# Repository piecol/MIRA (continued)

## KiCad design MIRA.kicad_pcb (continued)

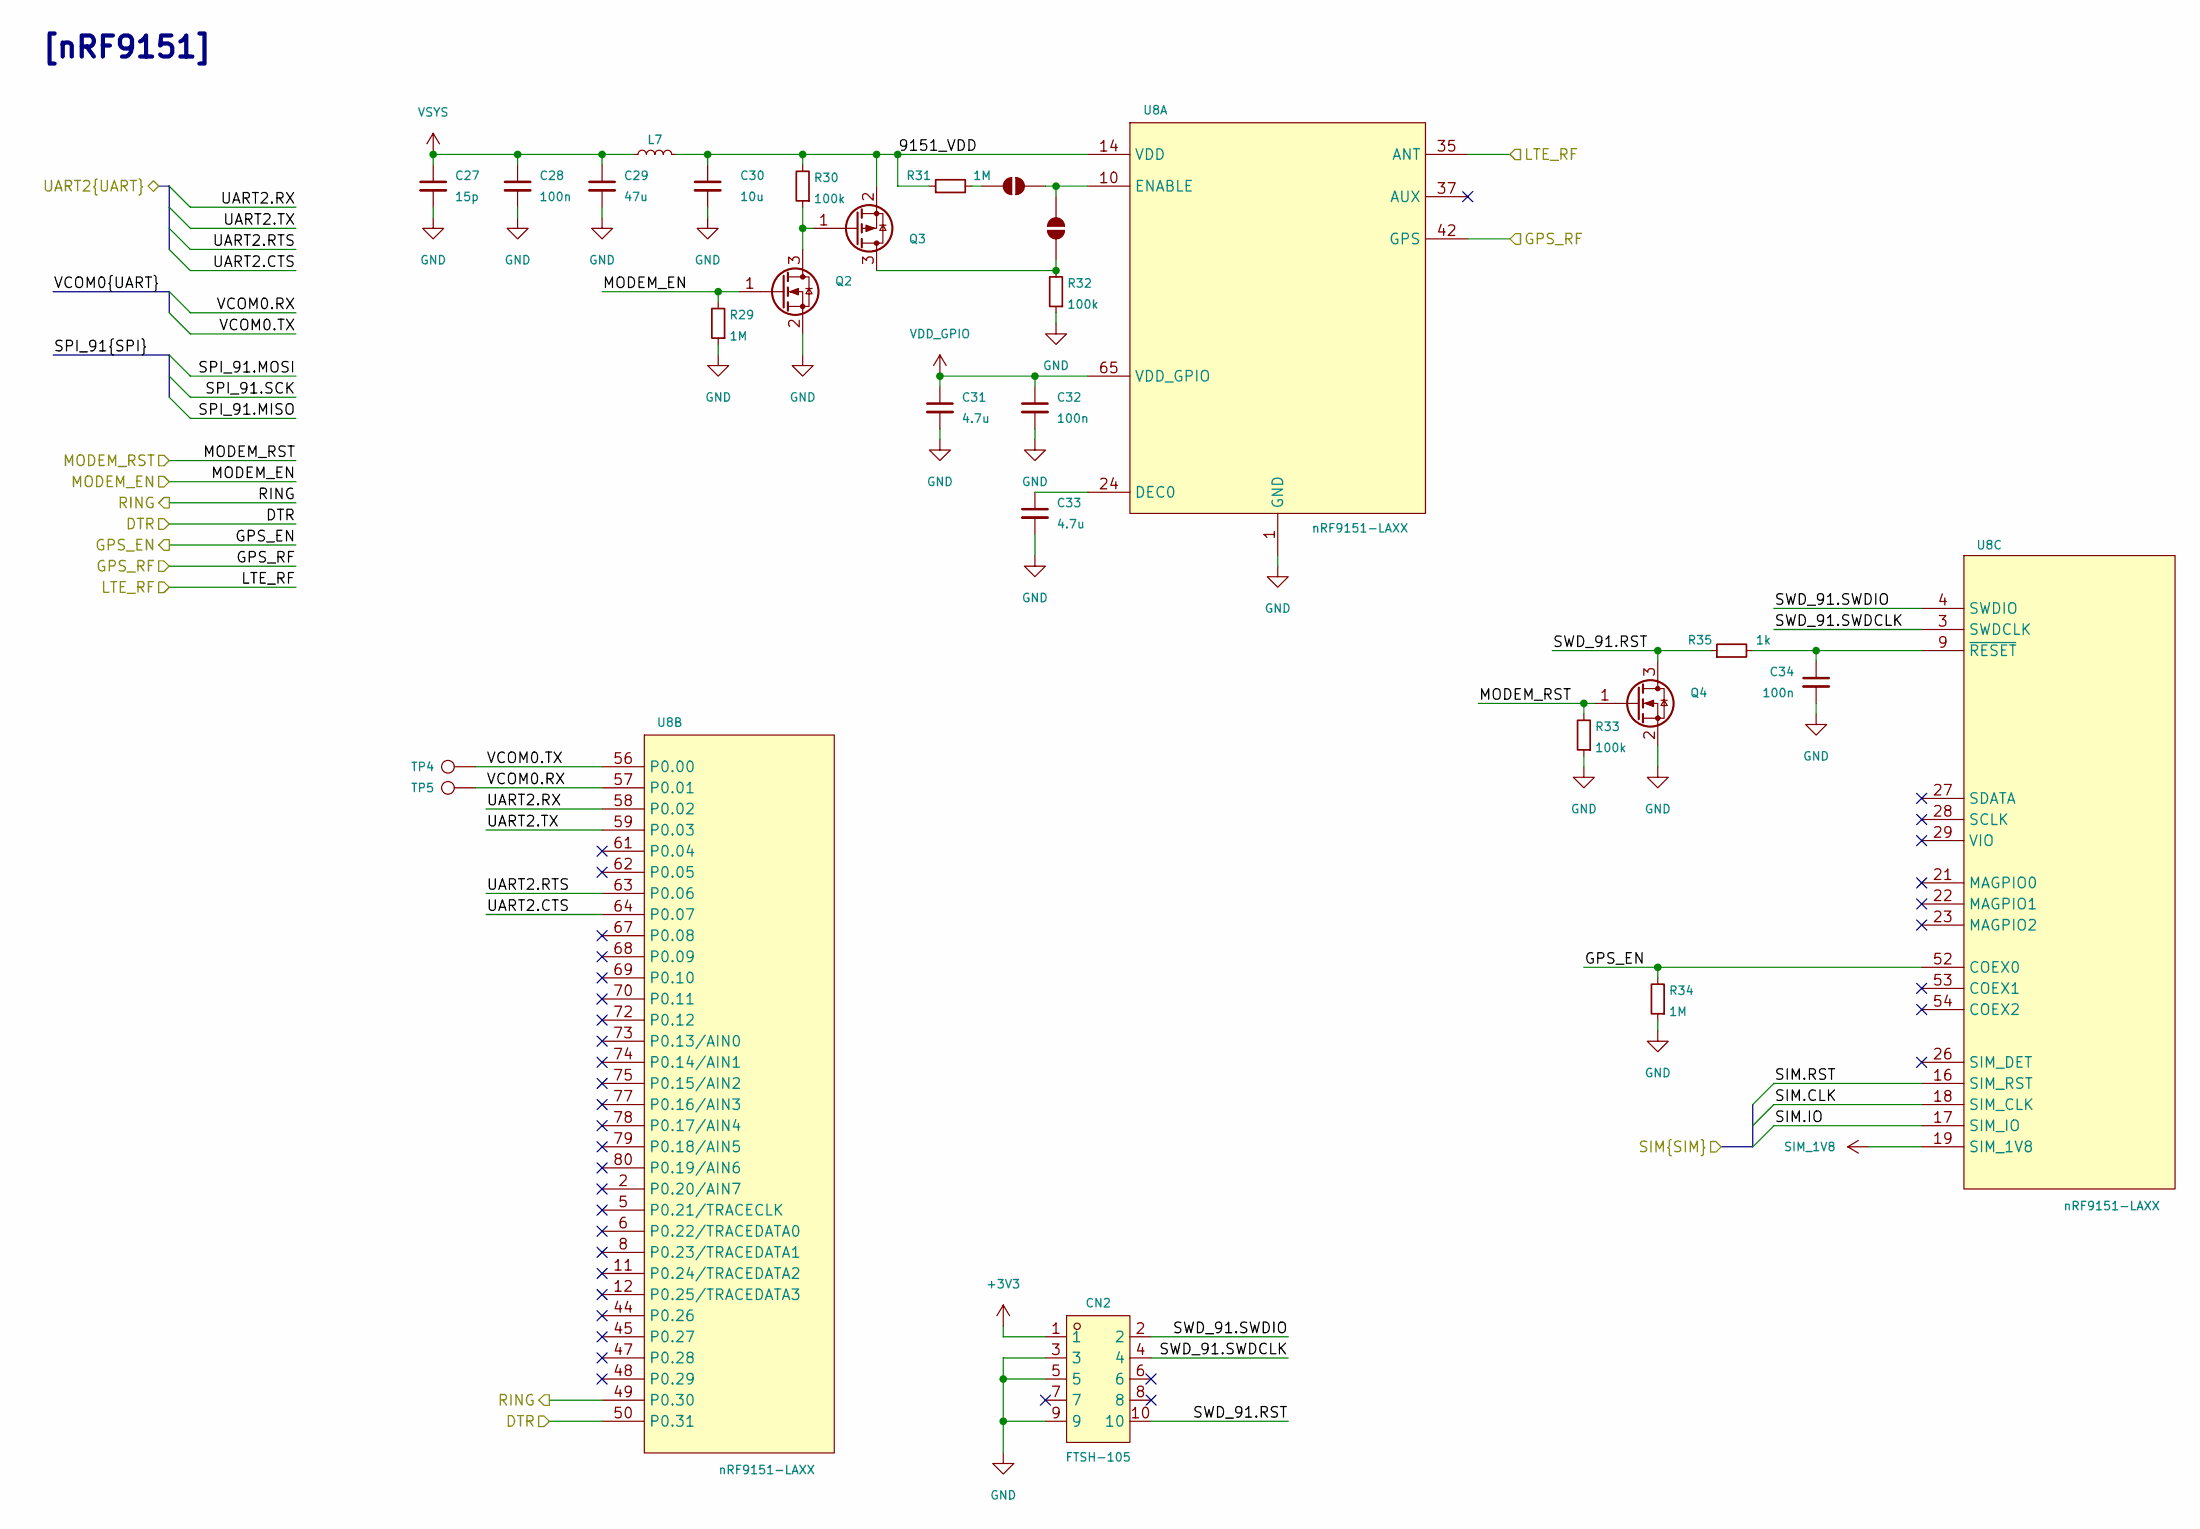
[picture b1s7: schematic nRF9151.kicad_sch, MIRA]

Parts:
C27: 15p; C_0402_1005Metric; LCSC C1548
C28, C32, C34: 100n; C_0402_1005Metric; LCSC C1525
C29: 47u; C_0805_2012Metric; LCSC C16780
C30: 10u; C_0402_1005Metric; LCSC C15525
C31, C33: 4.7u; C_0603_1608Metric; LCSC C19666
CN2: FTSH-105; CONN-SMD_FTSH-105-01-L-DV-K-TR; LCSC Part C448647
JP6, JP7: SolderJumper_2_Open; SolderJumper_Mini
L7: BLM15PX121SN1D; L_0402_1005Metric; LCSC Part C88970
Q2, Q4: DMN2990UFA-7B; XFDFN-3_L0.8-W0.6-P0.35-BR; MPN DMN2990UFA-7B; LCSC Part C151598
Q3: DMP22D4UFA-7B; X2-DFN0806-3_L0.8-W0.6-P0.35-BR; MPN DMP22D4UFA-7B; LCSC Part C2983692
R29, R31, R34: 1M; R_0402_1005Metric; LCSC C26083
R30, R32, R33: 100k; R_0402_1005Metric; LCSC C25741
R35: 1k; R_0402_1005Metric; LCSC C11702
TP4, TP5: TestPoint; TestPoint_Pad_D1.0mm
U8: nRF9151-LAXX; LGA_9151_12.1x11.1mm; LCSC C22397843

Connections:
+3V3: CN2.1; also elsewhere on the board
/RF/GPS_EN: R34.2, U8.52 (COEX0); also elsewhere on the board
/RF/GPS_RF: U8.42 (GPS); also elsewhere on the board
/RF/LTE_RF: U8.35 (ANT); also elsewhere on the board
/SIM/SIM.CLK: U8.18 (SIM_CLK); also elsewhere on the board
/SIM/SIM.IO: U8.17 (SIM_IO); also elsewhere on the board
/SIM/SIM.RST: U8.16 (SIM_RST); also elsewhere on the board
/nRF54L/DTR: U8.50 (P0.31); also elsewhere on the board
/nRF54L/MODEM_EN: Q2.1 (G), R29.2; also elsewhere on the board
/nRF54L/MODEM_RST: Q4.1 (G), R33.2; also elsewhere on the board
/nRF54L/RING: U8.49 (P0.30); also elsewhere on the board
/nRF54L/UARTE00.CTS: U8.64 (P0.07); also elsewhere on the board
/nRF54L/UARTE00.RTS: U8.63 (P0.06); also elsewhere on the board
/nRF54L/UARTE00.RX: U8.58 (P0.02); also elsewhere on the board
/nRF54L/UARTE00.TX: U8.59 (P0.03); also elsewhere on the board
/nRF9151/9151_VDD: C30.1, L7.2, Q3.2 (S), R30.2, R31.1, U8.14 (VDD)
/nRF9151/SWD_91.RST: CN2.10, Q4.3 (D), R35.1
/nRF9151/SWD_91.SWDCLK: CN2.4, U8.3 (SWDCLK)
/nRF9151/SWD_91.SWDIO: CN2.2, U8.4 (SWDIO)
/nRF9151/VCOM0.RX: TP5.1 (1_1), U8.57 (P0.01)
/nRF9151/VCOM0.TX: TP4.1 (1_1), U8.56 (P0.00)
GND: C27.2, C28.2, C29.2, C30.2, C31.2, C32.2, C33.2, C34.2, CN2.3, CN2.5, CN2.9, Q2.2 (S), Q4.2 (S), R29.1, R32.1, R33.1, R34.1, U8.1 (GND), U8.7 (GND), U8.13 (GND), U8.15 (GND), U8.20 (GND), U8.25 (GND), U8.30 (GND), U8.34 (GND), U8.36 (GND), U8.38 (GND), U8.39 (GND), U8.40 (GND), U8.41 (GND), U8.43 (GND), U8.46 (GND), U8.51 (GND), U8.55 (GND), U8.60 (GND), U8.66 (GND), U8.71 (GND), U8.76 (GND), U8.105 (GND), U8.106 (GND), U8.107 (GND), U8.108 (GND), U8.109 (GND), U8.110 (GND), U8.111 (GND), U8.112 (GND), U8.113 (GND); also elsewhere on the board
unnamed: JP6.1 (A), R31.2
unnamed: JP6.2 (B), JP7.1 (A), U8.10 (ENABLE)
unnamed: JP7.2 (B), Q3.3 (D), R32.2
unnamed: Q2.3 (D), Q3.1 (G), R30.1
unnamed: C33.1, U8.24 (DEC0)
unnamed: C34.1, R35.2, U8.9 (~RESET)
SIM_1V8: U8.19 (SIM_1V8); also elsewhere on the board
VDD_GPIO: C31.1, C32.1, U8.65 (VDD_GPIO); also elsewhere on the board
VSYS: C27.1, C28.1, C29.1, L7.1; also elsewhere on the board

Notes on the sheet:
[nRF9151]

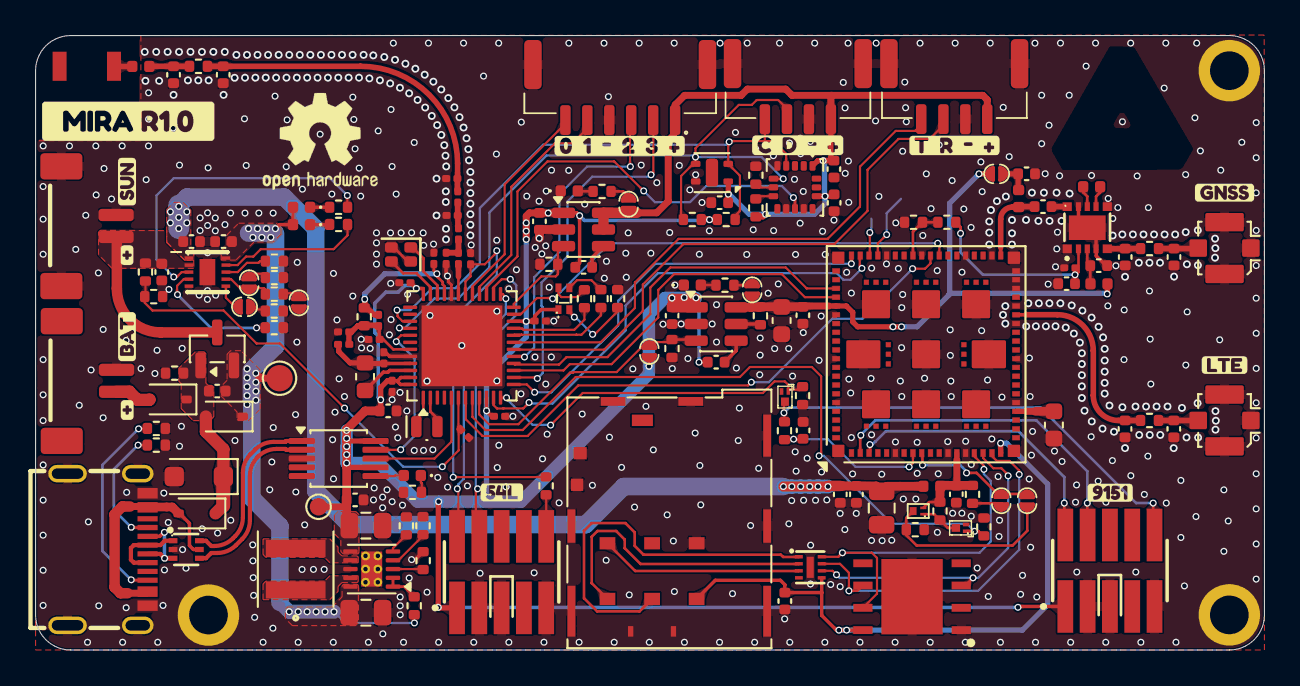
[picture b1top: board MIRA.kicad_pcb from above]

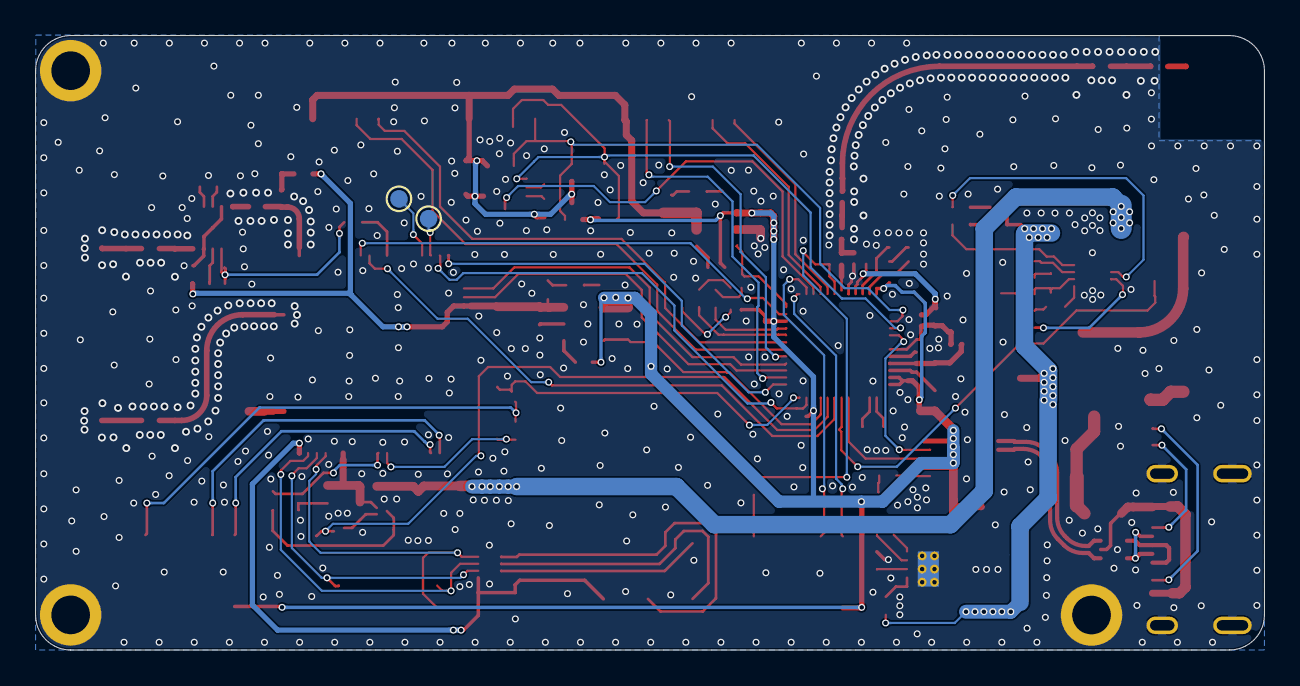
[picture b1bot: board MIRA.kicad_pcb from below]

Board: 4 copper layers, 70.0 x 35.0 mm, 171 parts (2 on the bottom side), 120 nets.

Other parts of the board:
kobee-studio-6ADCD3D5, kobee-studio-6ADCD3E6, kobee-studio-6ADCD3FA, kobee-studio-6ADCD3FA#2, kobee-studio-6ADCD5CB, kobee-studio-6ADCD5DB, kobee-studio-6ADCD7BB, kobee-studio-6ADCD7DD, kobee-studio-6ADCD390, kobee-studio-6ADCD606, kobee-studio-6ADCD613, kobee-studio-6ADCD849: Kobee Studio; kobee-studio-6ADCD390

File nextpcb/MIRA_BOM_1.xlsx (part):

Designator | MPN | Quantity | Value | Footprint | LCSC | Manufacturer | Description | Product link
L8 | LQW15AN68NG00D | 1 | 68nH | Inductor_SMD:L_0402_1005Metric | C108965 | Murata Electronics | 1.96Ω 140mA 68nH Unshielded Inductor ±2% 0402 Power Inductors ROHS | https://jlcpcb.com/partdetail/MurataElectronics-LQW15AN68NG0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
L9 | LQW15AN9N1G00D | 1 | 9.1nH | Inductor_SMD:L_0402_1005Metric | C113122 | Murata Electronics | 140mΩ 25@250MHz 5.5GHz 540mA 9.1nH ±2% 0402 Inductors (SMD) ROHS | https://jlcpcb.com/partdetail/MurataElectronics-LQW15AN9N1G0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
R7,R11,R12,R21,R35,R36 | 0402WGF1001TCE | 6 | 1k | Resistor_SMD:R_0402_1005Metric | C11702 | UNI-ROYAL(Uniroyal Elec) | -55℃~+155℃ 1kΩ 50V 62.5mW Thick Film Resistor ±1% ±100ppm/℃ 0402 Chip Resistor 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 | https://jlcpcb.com/partdetail/12256-0402WGF1001TCE/C11702
U10 | RFANT3216120A5T | 1 | RFANT3216120A5T | EasyEDA:FILTER-SMD_1206-2P-L3.2-W1.6-L | C127629 | Walsin Tech Corp | -40℃~+85℃ 1.2mm 1.55mm 1.6mm 100MHz 2 2.4GHz 2dBi 3.2mm 1206 Antennas ROHS | https://jlcpcb.com/partdetail/Walsin_TechCorp-RFANT3216120A5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
Q1 | AO3401A | 1 | AO3401A | Package_TO_SOT_SMD:SOT-23 | C15127 | Alpha & Omega Semicon | 1 P-Channel 14nC@10V 30V 47mΩ@10V、60mΩ@4.5V、85mΩ@2.5V 4A 55pF 645pF 80pF 900mV 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 | https://jlcpcb.com/partdetail/Alpha_OmegaSemicon-AO3401A/C15127
U11 | LIS3DHTR | 1 | LIS3DH | Package_LGA:LGA-16_3x3mm_P0.5mm_LayoutBorder3x5y | C15134 | STMicroelectronics | -40℃~+85℃ 1.71V~3.6V 16bit 500nA Accelerometer Motion event detection SPI、I2C X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 | https://jlcpcb.com/partdetail/STMicroelectronics-LIS3DHTR/C15134
Q2,Q4 | DMN2990UFA-7B | 2 | DMN2990UFA-7B | EasyEDA:XFDFN-3_L0.8-W0.6-P0.35-BR | C151598 | Diodes Incorporated | -55℃~+150℃ 1 N-channel 1V 2.4Ω@1.5V 20V 400mW 5.6pF 510mA 55.2pF 8pF N-Channel 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 | https://jlcpcb.com/partdetail/DiodesIncorporated-DMN2990UFA7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
U2 | TPS63900DSKR | 1 | TPS63900 | Package_SON:WSON-10-1EP_2.5x2.5mm_P0.5mm_EP1.2x2mm_ThermalVias | C1518762 | Texas Instruments | -40℃~+125℃@(TJ) 1 1.8V~5.5V 1.8V~5V 400mA 75nA Adjustable Buck-Boost Buck-Boost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 | https://jlcpcb.com/partdetail/TexasInstruments-TPS63900DSKR/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
C47 | CL05B103KB5NNNC | 1 | 10n | Capacitor_SMD:C_0402_1005Metric | C15195 | Samsung Electro-Mechanics | 10nF 50V X7R ±10% 0402 Multilayer Ceramic Capacitors MLCC - SMD/SMT ROHS | https://jlcpcb.com/partdetail/15869-CL05B103KB5NNNC/C15195
C3,C5,C28,C32,C34,C36,C39,C44,C45,C46 | CL05B104KO5NNNC | 10 | 100n | Capacitor_SMD:C_0402_1005Metric | C1525 | Samsung Electro-Mechanics | 100nF 16V X7R ±10% 0402 Multilayer Ceramic Capacitors MLCC - SMD/SMT ROHS | https://jlcpcb.com/partdetail/1877-CL05B104KO5NNNC/C1525
C27 | 0402CG150J500NT | 1 | 15p | Capacitor_SMD:C_0402_1005Metric | C1548 | FH (Guangdong Fenghua Advanced Tech) | 15pF 50V C0G ±5% 0402 Multilayer Ceramic Capacitors MLCC - SMD/SMT ROHS | https://jlcpcb.com/partdetail/1900-0402CG150J500NT/C1548
C6,C7,C12,C30,C50 | CL05A106MQ5NUNC | 5 | 10u | Capacitor_SMD:C_0402_1005Metric | C15525 | Samsung Electro-Mechanics | 10uF 6.3V X5R ±20% 0402 Multilayer Ceramic Capacitors MLCC - SMD/SMT ROHS | https://jlcpcb.com/partdetail/16204-CL05A106MQ5NUNC/C15525
C35,C37 | 0402CG390J500NT | 2 | 39p | Capacitor_SMD:C_0402_1005Metric | C1563 | FH (Guangdong Fenghua Advanced Tech) | 39pF 50V C0G ±5% 0402 Multilayer Ceramic Capacitors MLCC - SMD/SMT ROHS | https://jlcpcb.com/partdetail/1915-0402CG390J500NT/C1563
C21 | GRM0335C1E180GA01D | 1 | 18p | Capacitor_SMD:C_0201_0603Metric | C161374 | Murata Electronics | 18pF 25V C0G ±2% 0201 Multilayer Ceramic Capacitors MLCC - SMD/SMT ROHS | https://jlcpcb.com/partdetail/172755-GRM0335C1E180GA01D/C161374
C29 | CL21A476MQYNNNE | 1 | 47u | Capacitor_SMD:C_0805_2012Metric | C16780 | Samsung Electro-Mechanics | 47uF 6.3V X5R ±20% 0805 Multilayer Ceramic Capacitors MLCC - SMD/SMT ROHS | https://jlcpcb.com/partdetail/17464-CL21A476MQYNNNE/C16780
R5,R10,R28,R37,R38,R39 | 0402WGF0000TCE | 6 | 0R | Resistor_SMD:R_0402_1005Metric | C17168 | UNI-ROYAL(Uniroyal Elec) | -55℃~+155℃ 0Ω 50V 62.5mW Thick Film Resistor ±1% ±800ppm/℃ 0402 Chip Resistor -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 | https://jlcpcb.com/partdetail/17853-0402WGF0000TCE/C17168
D1,D2,D5 | 1N5819WS | 3 | 1N5819WS | Diode_SMD:D_SOD-323 | C191023 | Guangdong Hottech | 1 Independent 1A 25A 40V 500uA@40V 600mV@1A SOD-323 Schottky Diodes ROHS | https://jlcpcb.com/partdetail/GuangdongHottech-1N5819WS/C191023
U14 | SHTC3-TR-2.5KS | 1 | SHTC3 | Sensor_Humidity:Sensirion_DFN-4-1EP_2x2mm_P1mm_EP0.7x1.6mm | C194656 | Sensirion | -40℃~+125℃ 0%RH~100%RH 1.62V~3.6V 16bit 430uA Factory calibration、Temperature c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 | https://jlcpcb.com/partdetail/Sensirion-SHTC3_TR_25KS/C194656
C31,C33 | CL10A475KO8NNNC | 2 | 4.7u | Capacitor_SMD:C_0603_1608Metric | C19666 | Samsung Electro-Mechanics | 16V 4.7uF X5R ±10% 0603 Multilayer Ceramic Capacitors MLCC - SMD/SMT ROHS | https://jlcpcb.com/partdetail/20375-CL10A475KO8NNNC/C19666
U6 | BQ25185DLHR | 1 | BQ25185DLHR | EasyEDA:WSON-10_L2.2-W2.0-P0.40-BL-EP_TI_DLH0010A | C19725033 | Texas Instruments | -40℃~+125℃ 1 1A 2.2V 3V~18V 4.4V 4uA Charging IC Lithium Battery、LiFePO4 Batter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 | https://jlcpcb.com/partdetail/TexasInstruments-BQ25185DLHR/C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
L4,L5 | LQP03TN3N5B02D | 2 | 3.5nH | Inductor_SMD:L_0201_0603Metric | C206424 | Murata Electronics | 14@500MHz 250mΩ 3.5nH 450mA 7GHz Thick Film Inductor 0201 Inductors (SMD) ROHS | https://jlcpcb.com/partdetail/MurataElectronics-LQP03TN3N5B0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
D3,D6,D7,D8,D9 | XL-1005UBC | 5 | XL-1005UBC_C22355736 | LED_SMD:LED_0402_1005Metric | C22355736 | XINGLIGHT | -40℃~+85℃ 120° 20mA 240mcd 3.3V 455nm~475nm 465nm 70mW Blue Discrete Diode Top-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 | https://jlcpcb.com/partdetail/XINGLIGHT-XL1005UBC/C22355736
U8 | nRF9151-LACA-R7 | 1 | nRF9151-LAXX | PCM_nordic-lib-kicad-nrf9:LGA_9151_12.1x11.1mm | C22397843 | Nordic Semicon | LGA-113(12.1x11.1) RF Modules ROHS | https://jlcpcb.com/partdetail/NordicSemicon-nRF9151_LACAR7/C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
J2,J3 | CONUFL001-SMD-T | 2 | Conn_Coaxial_Small | Connector_Coaxial:U.FL_Molex_MCRF_73412-0110_Vertical | C22418213 | TE Connectivity | -40℃~+90℃ 1 50Ω 6GHz Board Side Male Pin SMD Coaxial Connectors (RF) ROHS | https://jlcpcb.com/partdetail/TEConnectivity-CONUFL001_SMDT/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
R22 | 0402WGF470KTCE | 1 | 4.7R | Resistor_SMD:R_0402_1005Metric | C25121 | UNI-ROYAL(Uniroyal Elec) | -55℃~+155℃ 4.7Ω 50V 62.5mW Thick Film Resistor ±1% ±200ppm/℃ 0402 Chip Resistor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 | https://jlcpcb.com/partdetail/25864-0402WGF470KTCE/C25121
R30,R32,R33 | 0402WGF1003TCE | 3 | 100k | Resistor_SMD:R_0402_1005Metric | C25741 | UNI-ROYAL(Uniroyal Elec) | -55℃~+155℃ 100kΩ 50V 62.5mW Thick Film Resistor ±1% ±100ppm/℃ 0402 Chip Resisto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 | https://jlcpcb.com/partdetail/26484-0402WGF1003TCE/C25741
R8,R16,R19,R40 | 0402WGF1002TCE | 4 | 10k | Resistor_SMD:R_0402_1005Metric | C25744 | UNI-ROYAL(Uniroyal Elec) | -55℃~+155℃ 10kΩ 50V 62.5mW Thick Film Resistor ±1% ±100ppm/℃ 0402 Chip Resistor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 | https://jlcpcb.com/partdetail/26487-0402WGF1002TCE/C25744
R42 | 0402WGF3303TCE | 1 | 330k | Resistor_SMD:R_0402_1005Metric | C25778 | UNI-ROYAL(Uniroyal Elec) | -55℃~+155℃ 330kΩ 50V 62.5mW Thick Film Resistor ±1% ±100ppm/℃ 0402 Chip Resisto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 | https://jlcpcb.com/partdetail/26521-0402WGF3303TCE/C25778
R6 | 0402WGF3652TCE | 1 | 36.5K | Resistor_SMD:R_0402_1005Metric | C25887 | UNI-ROYAL(Uniroyal Elec) | -55℃~+155℃ 36.5kΩ 50V 62.5mW Thick Film Resistor ±1% ±100ppm/℃ 0402 Chip Resist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 | https://jlcpcb.com/partdetail/26630-0402WGF3652TCE/C25887
R18,R20,R23,R24,R25,R26,R27 | 0402WGF4701TCE | 7 | 4.7k | Resistor_SMD:R_0402_1005Metric | C25900 | UNI-ROYAL(Uniroyal Elec) | -55℃~+155℃ 4.7kΩ 50V 62.5mW Thick Film Resistor ±1% ±100ppm/℃ 0402 Chip Resisto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 | https://jlcpcb.com/partdetail/26643-0402WGF4701TCE/C25900
R2,R3,R13 | 0402WGF5101TCE | 3 | 5.1k | Resistor_SMD:R_0402_1005Metric | C25905 | UNI-ROYAL(Uniroyal Elec) | -55℃~+155℃ 5.1kΩ 50V 62.5mW Thick Film Resistor ±1% ±100ppm/℃ 0402 Chip Resisto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 | https://jlcpcb.com/partdetail/26648-0402WGF5101TCE/C25905
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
